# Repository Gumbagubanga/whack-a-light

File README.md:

# Whack-A-Light - A DIY electronic whack-a-mole game

This project implements an electronic whack-a-mole style game with LED buttons.

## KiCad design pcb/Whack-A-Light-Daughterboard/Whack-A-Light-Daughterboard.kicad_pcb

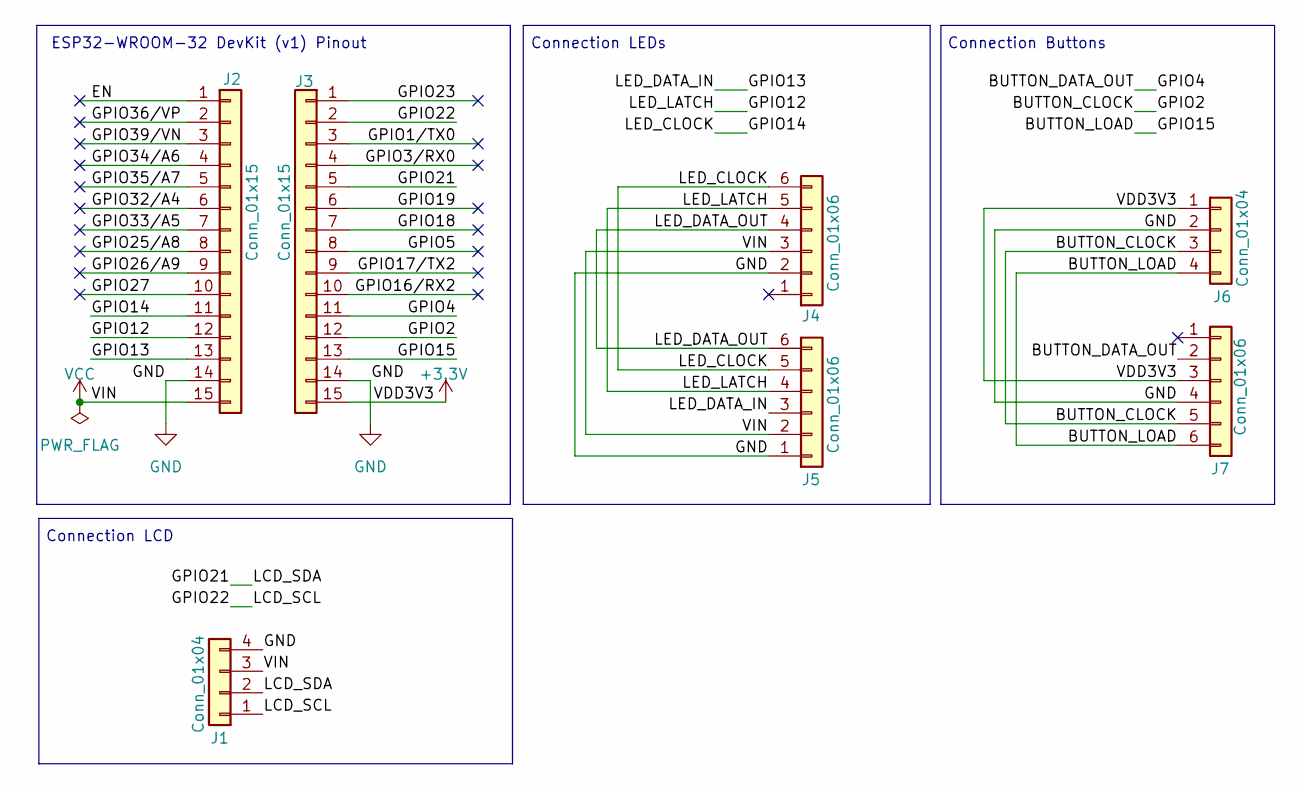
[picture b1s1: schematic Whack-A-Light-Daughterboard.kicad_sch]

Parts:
J1, J6: Conn_01x04; PinHeader_1x04_P2.54mm_Vertical
J2, J3: Conn_01x15; PinSocket_1x15_P2.54mm_Vertical
J4, J5, J7: Conn_01x06; PinHeader_1x06_P2.54mm_Vertical

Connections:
+3.3V: J3.15, J6.1, J7.3
/BUTTON_CLOCK: J3.12, J6.3, J7.5
/BUTTON_DATA_OUT: J3.11, J7.2
/BUTTON_LOAD: J3.13, J6.4, J7.6
/EN: J2.1
/GPIO1/TX0: J3.3
/GPIO3/RX0: J3.4
/GPIO5: J3.8
/GPIO12: J2.12, J4.5, J5.4
/GPIO13: J2.13, J5.3
/GPIO14: J2.11, J4.6, J5.5
/GPIO16/RX2: J3.10
/GPIO17/TX2: J3.9
/GPIO18: J3.7
/GPIO19: J3.6
/GPIO21: J1.2, J3.5
/GPIO22: J1.1, J3.2
/GPIO23: J3.1
/GPIO25/A8: J2.8
/GPIO26/A9: J2.9
/GPIO27: J2.10
/GPIO32/A4: J2.6
/GPIO33/A5: J2.7
/GPIO34/A6: J2.4
/GPIO35/A7: J2.5
/GPIO36/VP: J2.2
/GPIO39/VN: J2.3
/LED_DATA_OUT: J4.4, J5.6
GND: J1.4, J2.14, J3.14, J4.2, J5.1, J6.2, J7.4
VCC: J1.3, J2.15, J4.3, J5.2

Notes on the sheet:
Connection LEDs
Connection Buttons
Connection LCD
ESP32-WROOM-32 DevKit (v1) Pinout

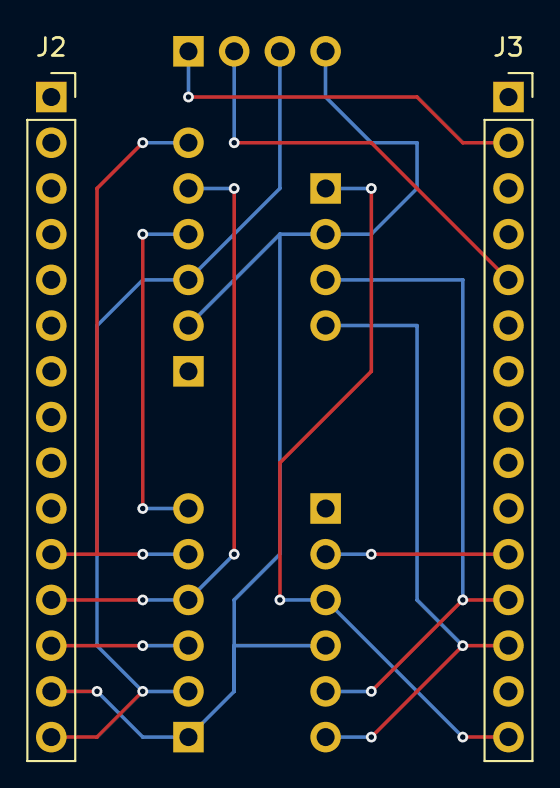
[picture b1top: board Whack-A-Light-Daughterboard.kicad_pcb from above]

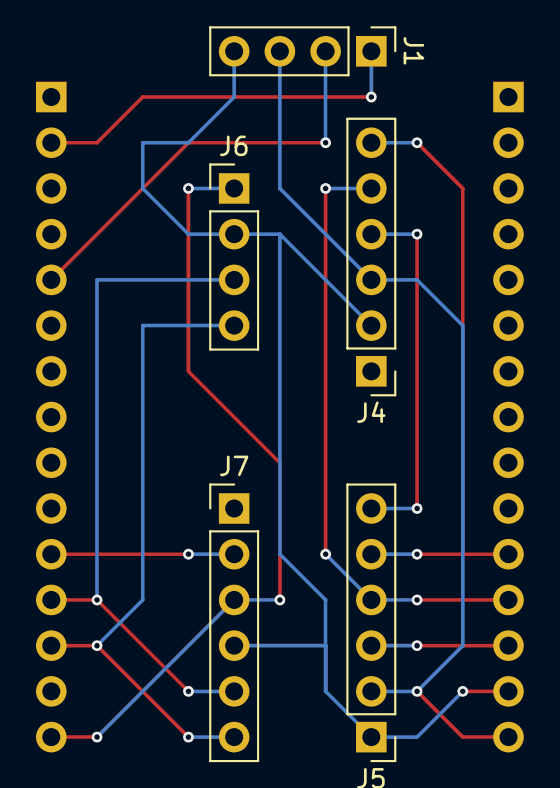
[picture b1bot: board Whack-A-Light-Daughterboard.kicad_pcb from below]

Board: 2 copper layers, 7 parts (5 on the bottom side), 12 nets.

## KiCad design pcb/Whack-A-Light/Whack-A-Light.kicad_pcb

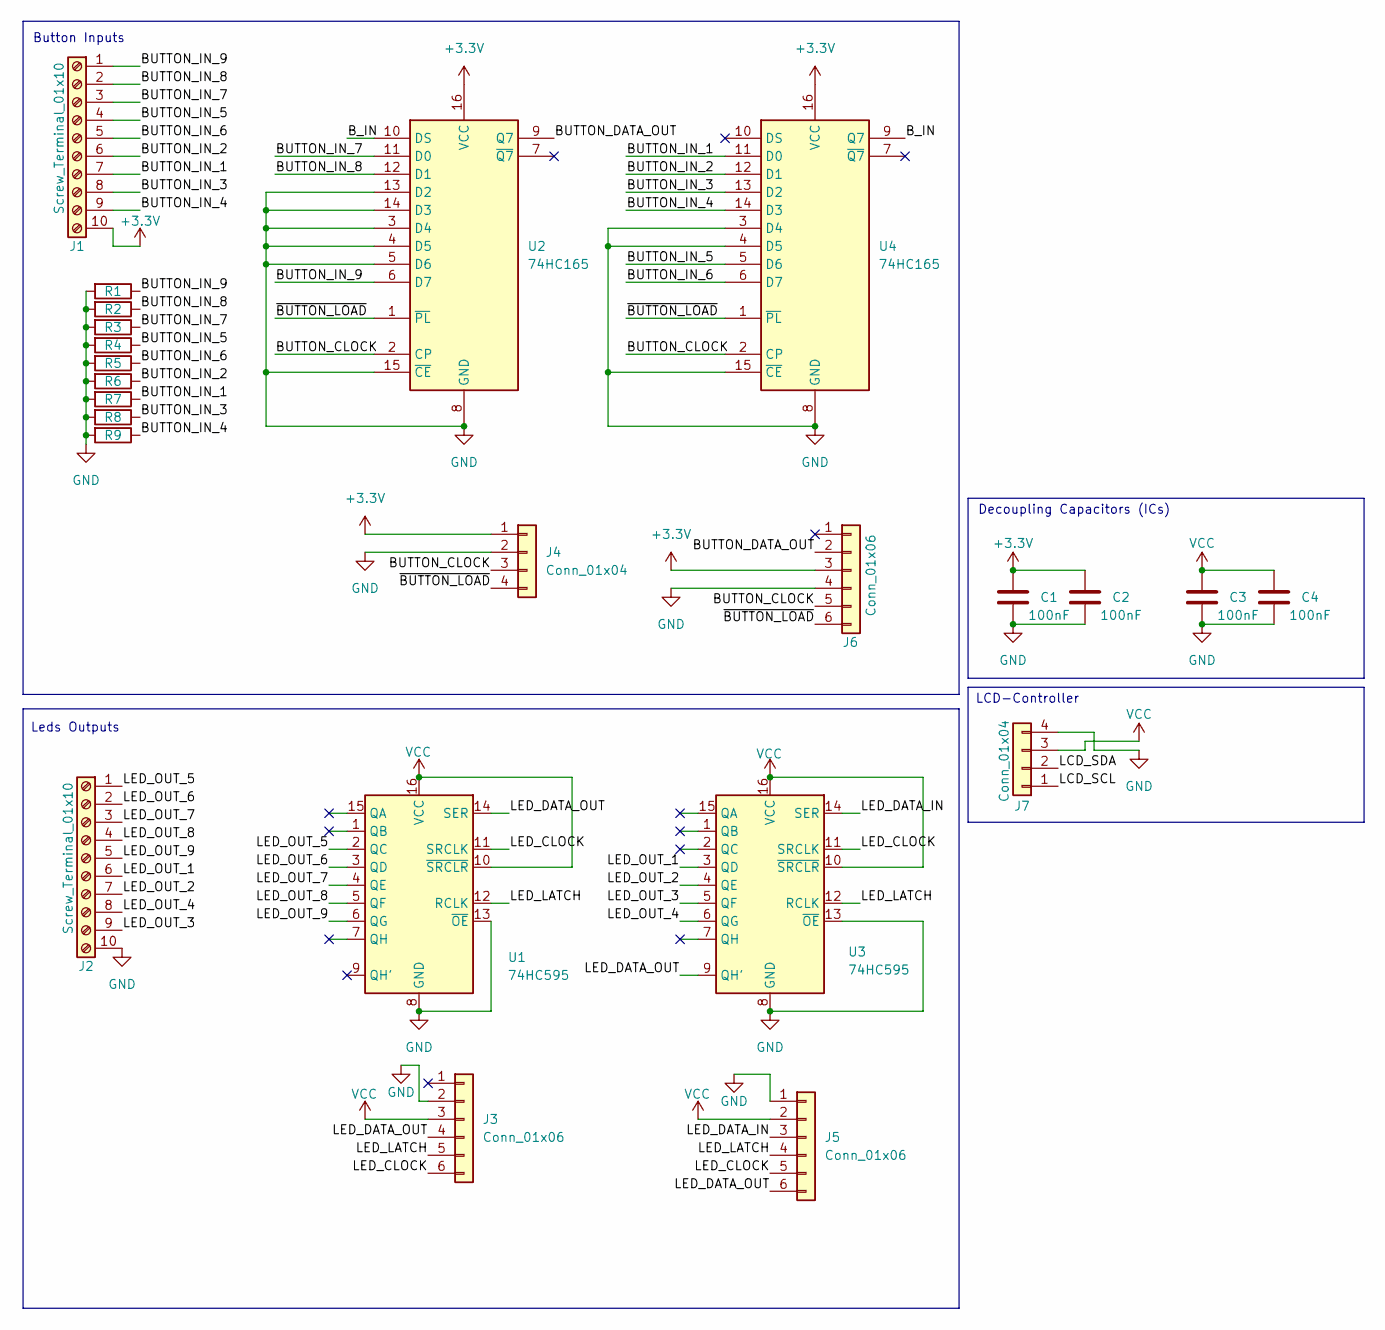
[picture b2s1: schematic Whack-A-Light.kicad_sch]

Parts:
C1, C2, C3, C4: 100nF; C_Disc_D3.0mm_W2.0mm_P2.50mm
J1, J2: Screw_Terminal_01x10; TerminalBlock_Phoenix_MKDS-1,5-10-5.08_1x10_P5.08mm_Horizon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
J3, J5, J6: Conn_01x06; PinSocket_1x06_P2.54mm_Vertical
J4: Conn_01x04; PinSocket_1x04_P2.54mm_Vertical
J7: Conn_01x04; PinHeader_1x04_P2.54mm_Horizontal
R1, R2, R3, R4, R5, R6, R7, R8, R9: 10k Ohm; R_Axial_DIN0204_L3.6mm_D1.6mm_P5.08mm_Horizontal
U1, U3: 74HC595; DIP-16_W7.62mm_Socket
U2, U4: 74HC165; DIP-16_W7.62mm_Socket

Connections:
+3.3V: C1.2, C2.1, J1.10, J4.1, J6.3, U2.16 (VCC), U4.16 (VCC)
/BUTTON_CLOCK: J4.3, J6.5, U2.2 (CP), U4.2 (CP)
/BUTTON_DATA_OUT: J6.2, U2.9 (Q7)
/BUTTON_IN_1: J1.7, R7.1, U4.11 (D0)
/BUTTON_IN_2: J1.6, R6.1, U4.12 (D1)
/BUTTON_IN_3: J1.8, R8.1, U4.13 (D2)
/BUTTON_IN_4: J1.9, R9.1, U4.14 (D3)
/BUTTON_IN_5: J1.4, R4.1, U4.5 (D6)
/BUTTON_IN_6: J1.5, R5.1, U4.6 (D7)
/BUTTON_IN_7: J1.3, R3.1, U2.11 (D0)
/BUTTON_IN_8: J1.2, R2.1, U2.12 (D1)
/BUTTON_IN_9: J1.1, R1.1, U2.6 (D7)
/B_IN: U2.10 (DS), U4.9 (Q7)
/LCD_SCL: J7.1; also elsewhere on the board
/LCD_SDA: J7.2; also elsewhere on the board
/LED_CLOCK: J3.6, J5.5, U1.11 (SRCLK), U3.11 (SRCLK)
/LED_DATA_IN: J5.3, U3.14 (SER)
/LED_DATA_OUT: J3.4, J5.6, U1.14 (SER), U3.9 (QH')
/LED_LATCH: J3.5, J5.4, U1.12 (RCLK), U3.12 (RCLK)
/LED_OUT_1: J2.6, U3.3 (QD)
/LED_OUT_2: J2.7, U3.4 (QE)
/LED_OUT_3: J2.9, U3.5 (QF)
/LED_OUT_4: J2.8, U3.6 (QG)
/LED_OUT_5: J2.1, U1.2 (QC)
/LED_OUT_6: J2.2, U1.3 (QD)
/LED_OUT_7: J2.3, U1.4 (QE)
/LED_OUT_8: J2.4, U1.5 (QF)
/LED_OUT_9: J2.5, U1.6 (QG)
/~BUTTON_LOAD: J4.4, J6.6, U2.1 (~PL), U4.1 (~PL)
GND: C1.1, C2.2, C3.1, C4.2, J2.10, J3.2, J4.2, J5.1, J6.4, J7.4, R1.2, R2.2, R3.2, R4.2, R5.2, R6.2, R7.2, R8.2, R9.2, U1.8 (GND), U1.13 (~OE), U2.3 (D4), U2.4 (D5), U2.5 (D6), U2.8 (GND), U2.13 (D2), U2.14 (D3), U2.15 (~CE), U3.8 (GND), U3.13 (~OE), U4.3 (D4), U4.4 (D5), U4.8 (GND), U4.15 (~CE); also elsewhere on the board
VCC: C3.2, C4.1, J3.3, J5.2, J7.3, U1.10 (~SRCLR), U1.16 (VCC), U3.10 (~SRCLR), U3.16 (VCC); also elsewhere on the board

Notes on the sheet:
LCD-Controller
Decoupling Capacitors (ICs)
Leds Outputs
Button Inputs

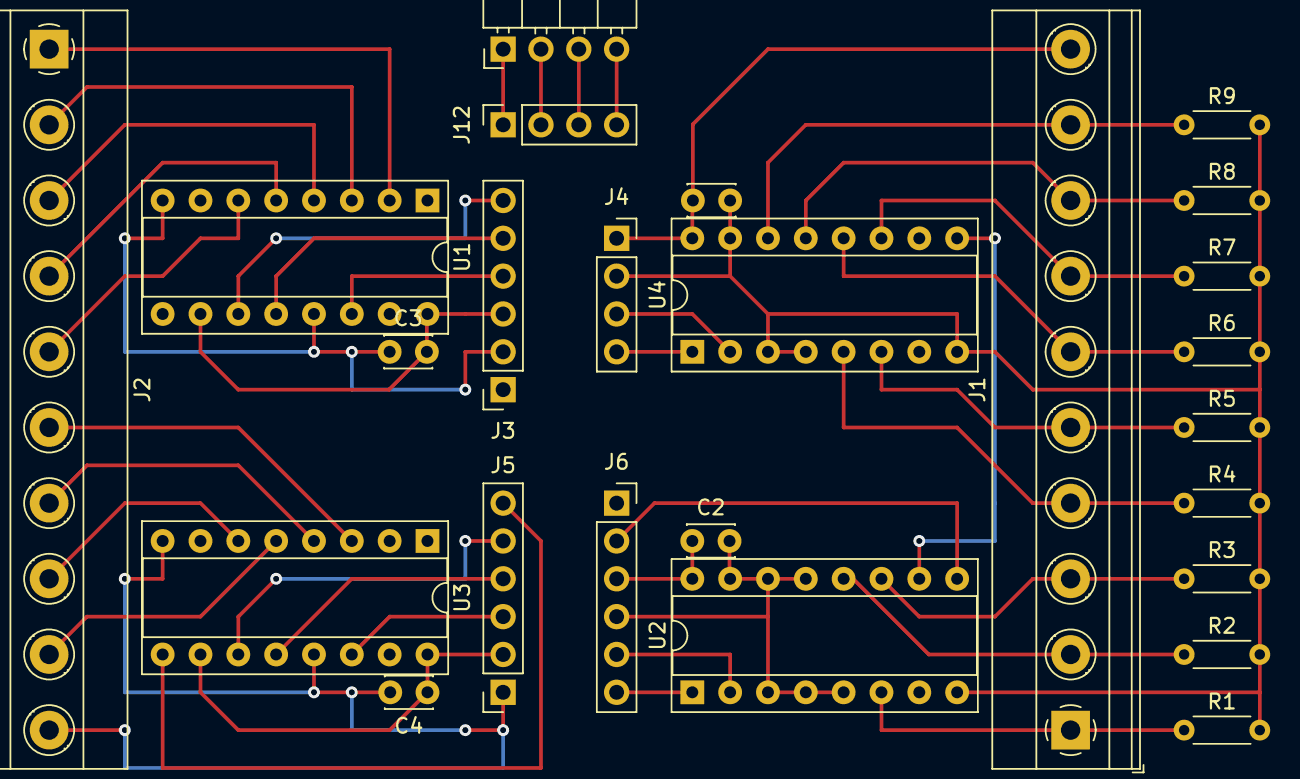
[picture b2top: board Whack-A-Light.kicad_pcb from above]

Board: 2 copper layers, 25 parts (0 on the bottom side), 31 nets.

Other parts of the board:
J12: Conn_01x04; PinSocket_1x04_P2.54mm_Vertical

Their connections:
/LCD_SCL: J12.1; also elsewhere on the board
/LCD_SDA: J12.2; also elsewhere on the board
GND: J12.4; also elsewhere on the board
VCC: J12.3; also elsewhere on the board

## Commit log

2024-12-05 First implementation
2024-12-05 First PCB KiCad Designs
